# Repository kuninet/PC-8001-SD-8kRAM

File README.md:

# PC-8001 8kB SRAM/MicroSD/RTCボード

## 概要

* PC-8001 拡張CPUバスにつながる8kB SRAM、MicroSD、RTC搭載ボードです。
* SD-DOSが動きます。

## 部品表
* 部品表は以下のCSVファイルを参照ください。
  * [部品表](KiCAD/PC8001-SD-8kRAM.csv)

## 回路図

## 稼働させる際の注意 
### ★電圧調整の際はテスタで計測しながら、トリマは慎重にまわしてください。ちょっと動かすだけで6Vなどの電圧が出ます。PC-8001のメインボードのICが壊れる可能性があります。

* PC-8001の電源電圧が下がっている場合があります。外部基板としてつなげた本基板にきている電圧が4.5Vなどになっていると安定しません。PC-8001の電源ユニット内の調整トリマを回して5V程度出るようにしてください。
* [2022/1/8追記] 回路図のツェナーダイオードの定格をRD4.2 → RD3.6としました。本体電圧を調整することなく安定すると思われます。

## 参考

* SD-DOS
  * https://github.com/chiqlappe/SD-DOS
* PC-8001 MicroSDボード
  * https://github.com/chiqlappe/sdd
* PC-8001 8k SRAMボード
  * https://github.com/chiqlappe/ram8k
* PC8001 RTCドライバー
  * https://github.com/chiqlappe/rtc

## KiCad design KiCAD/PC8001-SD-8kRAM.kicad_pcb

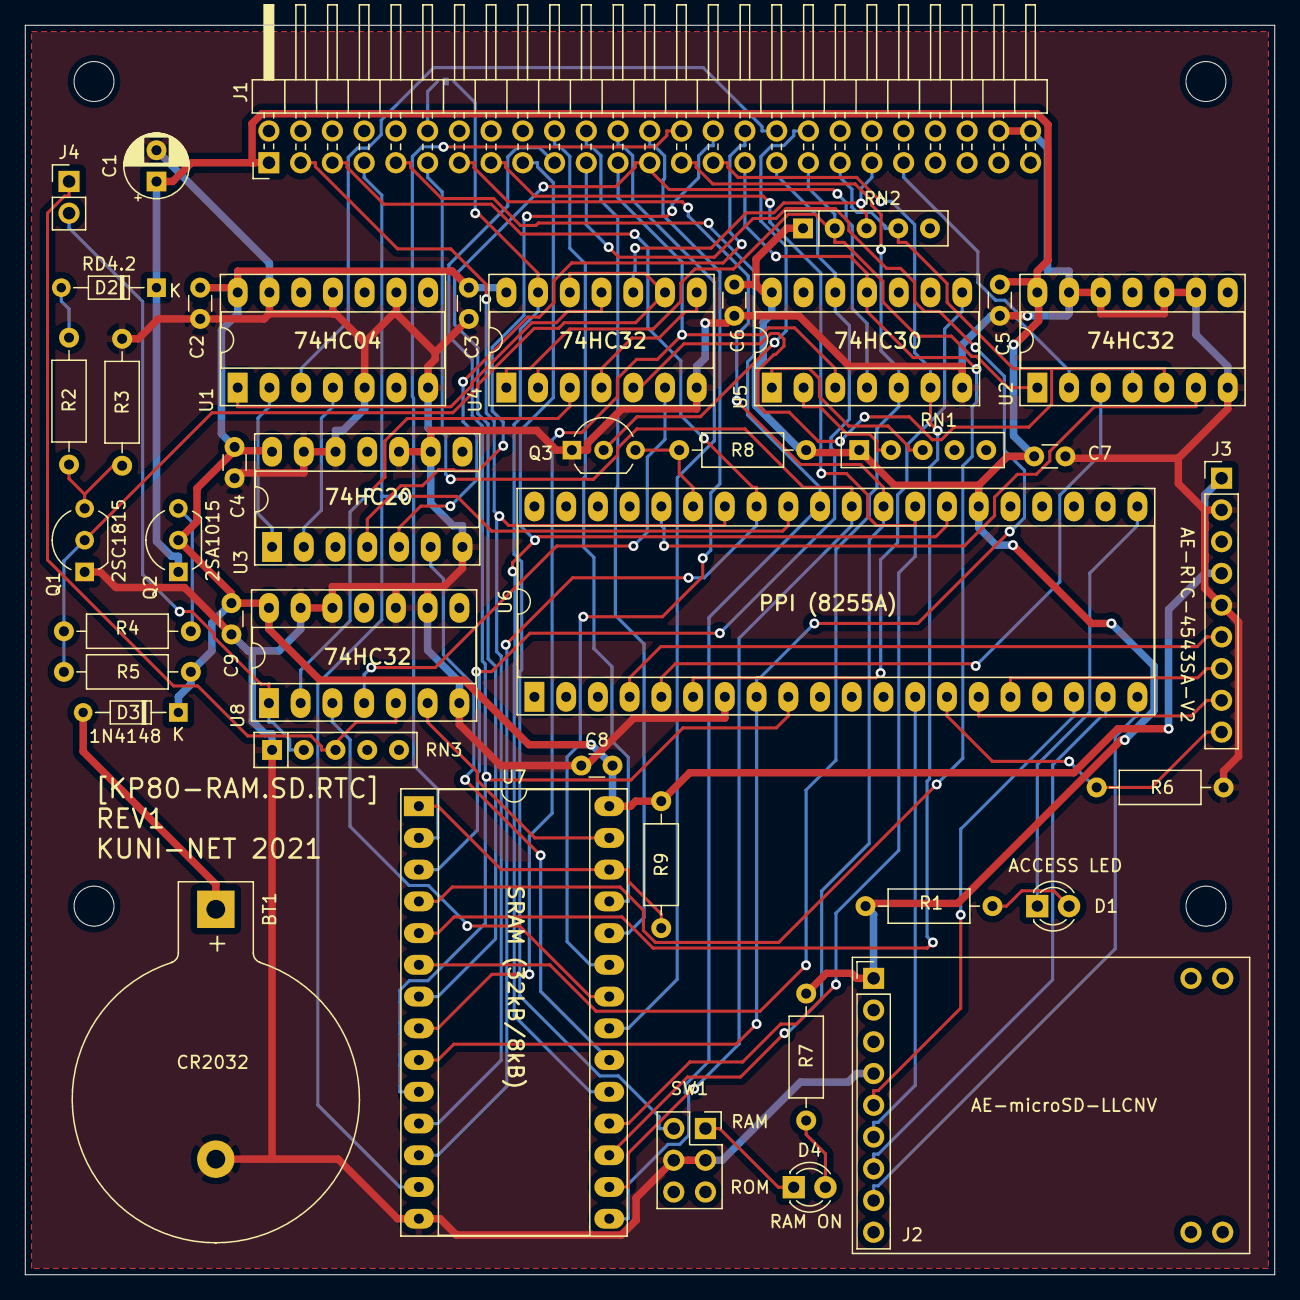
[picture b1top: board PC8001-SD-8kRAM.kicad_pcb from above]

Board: 2 copper layers, 100.0 x 100.0 mm, 47 parts (1 on the bottom side), 69 nets.

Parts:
BT1: CR2032; BatteryHolder_20mmwide
C1: 10u; CP_Radial_D5.0mm_P2.50mm
C2, C3, C4, C5, C6, C7, C8, C9: 0.1u; C_Disc_D3.0mm_W1.6mm_P2.50mm
D1: ACCESS LED; LED_D3.0mm
D2: RD4.2; D_DO-34_SOD68_P7.62mm_Horizontal
D3: 1N4148; D_DO-34_SOD68_P7.62mm_Horizontal
D4: RAM ON; LED_D3.0mm
J1: PC-8001 ext BUS; PinHeader_2x25_P2.54mm_Horizontal
J2: AE-microSD-LLCNV
J3: AE-RTC-4543SA-V2; PinHeader_1x09_P2.54mm_Vertical
J4: 128k MEM CTL; PinHeader_1x02_P2.54mm_Vertical
JP1: ROM_JP; SolderJumper-2_P1.3mm_Bridged_RoundedPad1.0x1.5mm
MH1, MH2, MH3, MH4: MountingHole; MountingHole_3.2mm_M3
Q1: 2SC1815; TO-92_Inline_Wide
Q2: 2SA1015; TO-92_Inline_Wide
Q3: 2N7000; TO-92_Inline_Wide
R1, R2, R7: 1k; R_Axial_DIN0207_L6.3mm_D2.5mm_P10.16mm_Horizontal
R3: 1.2k; R_Axial_DIN0207_L6.3mm_D2.5mm_P10.16mm_Horizontal
R4: 2.2k; R_Axial_DIN0207_L6.3mm_D2.5mm_P10.16mm_Horizontal
R5: 22k; R_Axial_DIN0207_L6.3mm_D2.5mm_P10.16mm_Horizontal
R6: 4.7k; R_Axial_DIN0207_L6.3mm_D2.5mm_P10.16mm_Horizontal
R8: 1M; R_Axial_DIN0207_L6.3mm_D2.5mm_P10.16mm_Horizontal
R9: 10k; R_Axial_DIN0207_L6.3mm_D2.5mm_P10.16mm_Horizontal
RN1, RN2, RN3: 10k; R_Array_SIP5
SW1: RAM SW; SS-22SDP2
U1: 74HC04; DIP-14_W7.62mm_Socket_LongPads
U2, U4, U8: 74HC32; DIP-14_W7.62mm_Socket_LongPads
U3: 74HC20; DIP-14_W7.62mm_Socket_LongPads
U5: 74HC30; DIP-14_W7.62mm_Socket_LongPads
U6: 8255A; DIP-40_W15.24mm_Socket_LongPads
U7: 256kRAM; DIP-28_W15.24mm_Socket_LongPads

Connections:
+5V: C2.2, C3.2, C4.2, C8.2, C9.2, D3.1, J3.1, J3.4, Q2.2, R5.1, R9.1, U1.14, U3.14, U4.14, U7.28, U8.14
/A0: J1.19, U6.9, U7.10
/A1: J1.21, U6.8, U7.9
/A2: J1.23, U5.3, U7.8
/A3: J1.25, U5.4, U7.7
/A4: J1.27, U5.5, U7.6
/A5: J1.29, U5.6, U7.5
/A6: J1.31, U5.11, U7.4
/A7: J1.33, U5.12, U7.3
/A8: J1.20, U7.25
/A9: J1.22, U7.24
/A10: J1.24, U7.21
/A11: J1.26, U7.23
/A12: J1.28, U7.2
/A13: J1.30, U3.4
/A14: J1.32, U3.5
/A15: J1.34, U1.3
/CMD: J2.7, U6.19
/CS2: R9.2, U7.1, U7.26
/D0: J1.3, U6.34, U7.11
/D1: J1.5, U6.33, U7.12
/D2: J1.7, U6.32, U7.13
/D3: J1.9, U6.31, U7.15
/D4: J1.11, U6.30, U7.16
/D5: J1.13, U6.29, U7.17
/D6: J1.15, U6.28, U7.18
/D7: J1.17, U6.27, U7.19
/E2#D0: J4.2, RN3.2, U8.1
/E2#D4: J4.1, RN3.3, U8.5
/RTC_CE: J3.9, R6.1, U6.14
/RTC_CLK: J3.7, U6.16
/RTC_DIN: J3.6, U6.4
/RTC_WR: J3.8, U6.15
/SDCLK: J2.5, U6.18
/SDCS: J2.8, U6.20
/SDDAT: J2.6, U6.13
/~CS1: U3.6, U7.20
/~IORD: U2.3, U6.5
/~IOREQ: J1.41, U2.2, U2.4
/~IOWR: U2.6, U6.36
/~MRD: U7.22, U8.3
/~MREQ: J1.39, RN2.3, U4.10
/~MWR: U7.27, U8.6
/~RD: J1.35, RN2.2, U2.1, U4.1
/~RESET: J1.36, Q3.2
/~ROMDS3: J1.12, JP1.1
/~VCC_ON: Q1.2, R4.2, R5.2, U4.9, U4.12
/~WR: J1.37, RN2.4, U2.5, U4.5
GND: BT1.2, C1.2, C2.1, C3.1, C4.1, C5.1, C6.1, C7.1, C8.1, C9.1, J1.48, J1.50, J2.4, J3.2, J3.5, Q1.1, Q3.1, R3.2, R6.2, RN3.1, SW1.2, SW1.5, U1.5, U1.7, U1.9, U1.11, U1.13, U2.7, U2.9, U2.10, U2.12, U2.13, U3.7, U3.9, U3.10, U3.12, U3.13, U4.7, U5.7, U6.7, U7.14, U8.7, U8.9, U8.10, U8.12, U8.13
unnamed: BT1.1, D3.2
unnamed: D1.1, U6.21
unnamed: D1.2, R1.2
unnamed: D2.2, R2.1
unnamed: D4.1, SW1.1
unnamed: D4.2, R7.2
unnamed: JP1.2, SW1.4, U4.13
unnamed: Q1.3, R2.2, R3.1
unnamed: Q2.3, R4.1
unnamed: Q3.3, R8.2, U6.35
unnamed: RN1.2, U5.2
unnamed: RN1.3, U5.1
unnamed: U1.1, U4.11
unnamed: U1.2, U3.1
unnamed: U1.4, U3.2
unnamed: U4.2, U4.4, U4.8
unnamed: U4.3, U8.2
unnamed: U4.6, U8.4
unnamed: U5.8, U6.6
VCC: C1.1, C5.2, C6.2, C7.2, D2.1, J1.1, J2.1, Q2.1, R1.1, R7.1, R8.1, RN1.1, RN2.1, U2.14, U5.14, U6.26

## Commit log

2021-08-29 init
2021-08-29 Create LICENSE
2021-08-29 README追記
2021-08-29 ROMDS3切り離し用ジャンパパッド追加
2021-12-08 READMEの詳細化。回路図イメージ追加
2022-01-09 回路図のツェナーダイオード定格を変更 RD4.2→RD3.6
